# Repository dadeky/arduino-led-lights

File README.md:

# arduino-led-lights
C++ Arduino application that manages led lights dimming

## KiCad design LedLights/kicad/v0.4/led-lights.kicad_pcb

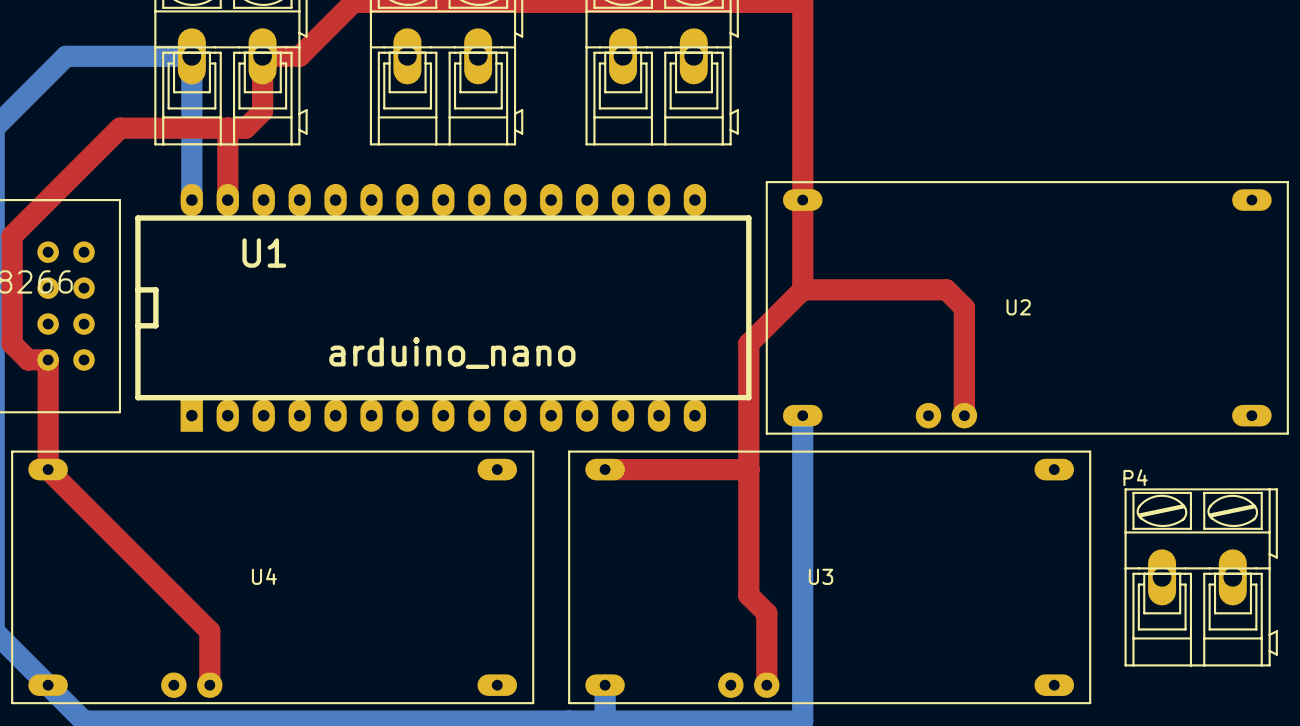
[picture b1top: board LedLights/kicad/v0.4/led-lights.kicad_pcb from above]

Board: 2 copper layers, 9 parts (0 on the bottom side), 13 nets.

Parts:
P1: Power input; AK300-2
P3: LED 1; AK300-2
P4: LED 2; AK300-2
P5: LED 3; AK300-2
U1: arduino_nano
U2, U3, U4: LED_Driver_700mA; LED_Driver_700mA_foot
U5: Wlan_ESP8266

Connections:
+12V: P1.1, U1.VIN, U2.1, U3.1, U4.1
GND: P1.2, U1.GND, U2.2, U2.6, U3.2, U3.6, U4.2, U4.6, U5.GND
unnamed: P3.1, U2.3
unnamed: P3.2, U2.4
unnamed: P4.1, U3.3
unnamed: P4.2, U3.4
unnamed: P5.1, U4.3
unnamed: P5.2, U4.4
ledPwmPin1: U1.D3, U2.5
ledPwmPin2: U1.D5, U3.5
ledPwmPin3: U1.D6, U4.5
wlanRX: U1.D7, U5.RX
wlanTX: U1.D4, U5.TX

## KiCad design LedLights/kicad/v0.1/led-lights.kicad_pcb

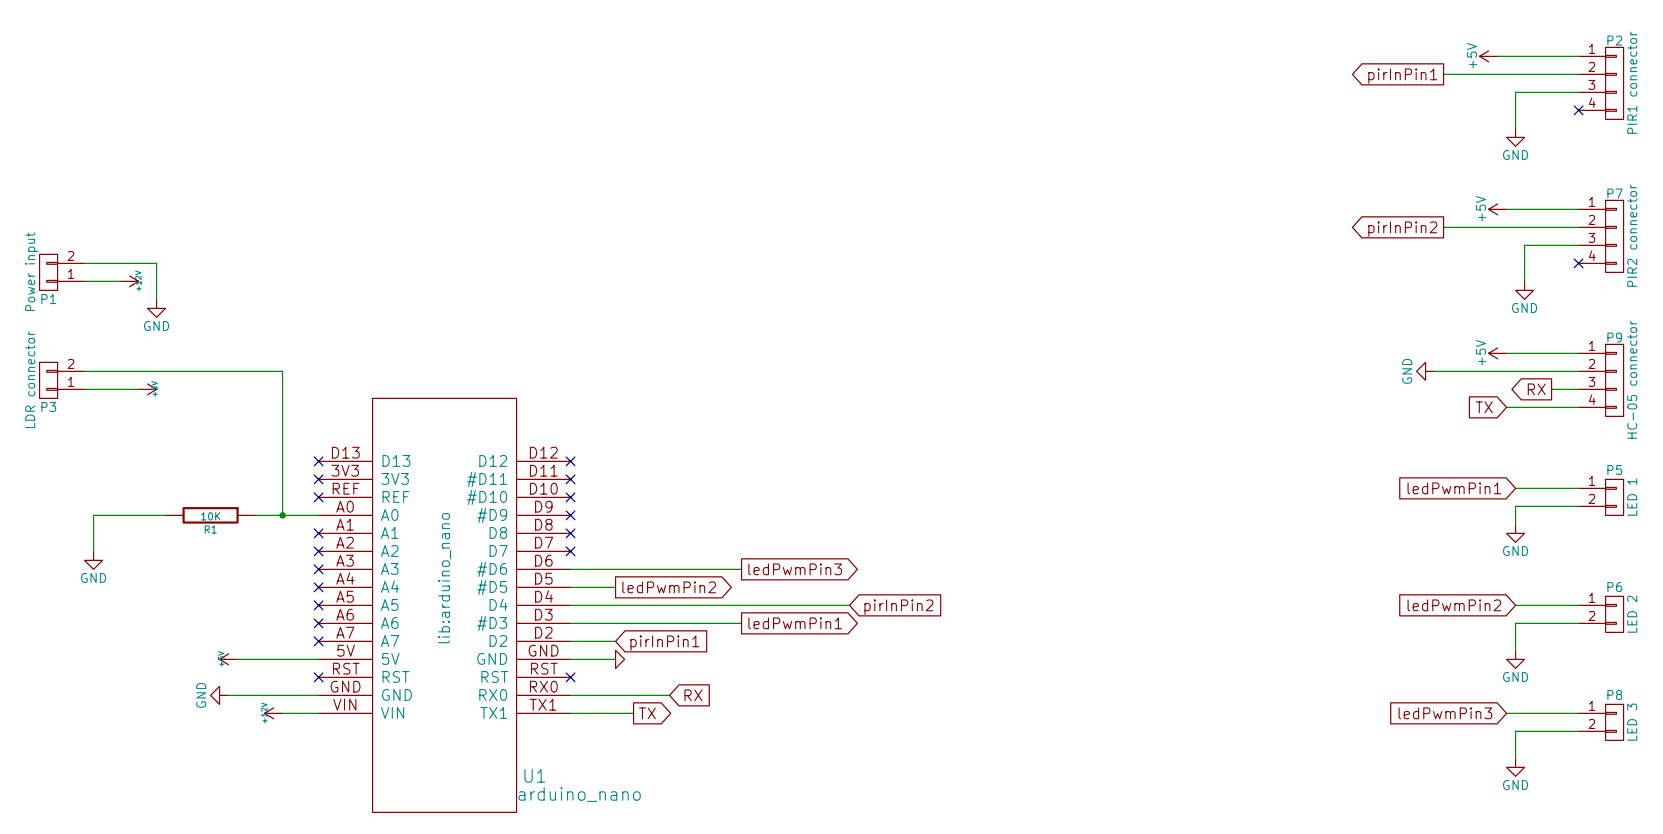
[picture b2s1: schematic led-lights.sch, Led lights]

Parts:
P1: Power input; AK300-2
P2: PIR1 connector; AK300-4
P3: LDR connector; AK300-2
P5: LED 1; AK300-2
P6: LED 2; AK300-2
P7: PIR2 connector; AK300-4
P8: LED 3; AK300-2
P9: HC-05 connector; Socket_Strip_Straight_1x04
R1: 10K; Resistor_Horizontal_RM15mm
U1: arduino_nano

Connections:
+5V: P2.1, P3.1, P7.1, P9.1, U1.5V
+12V: P1.1, U1.VIN
GND: P1.2, P2.3, P5.2, P6.2, P7.3, P8.2, P9.2, R1.2, U1.GND
unnamed: P3.2, R1.1, U1.A0
RX: P9.3, U1.RX0
TX: P9.4, U1.TX1
ledPwmPin1: P5.1, U1.D3 (#D3)
ledPwmPin2: P6.1, U1.D5 (#D5)
ledPwmPin3: P8.1, U1.D6 (#D6)
pirInPin1: P2.2, U1.D2
pirInPin2: P7.2, U1.D4

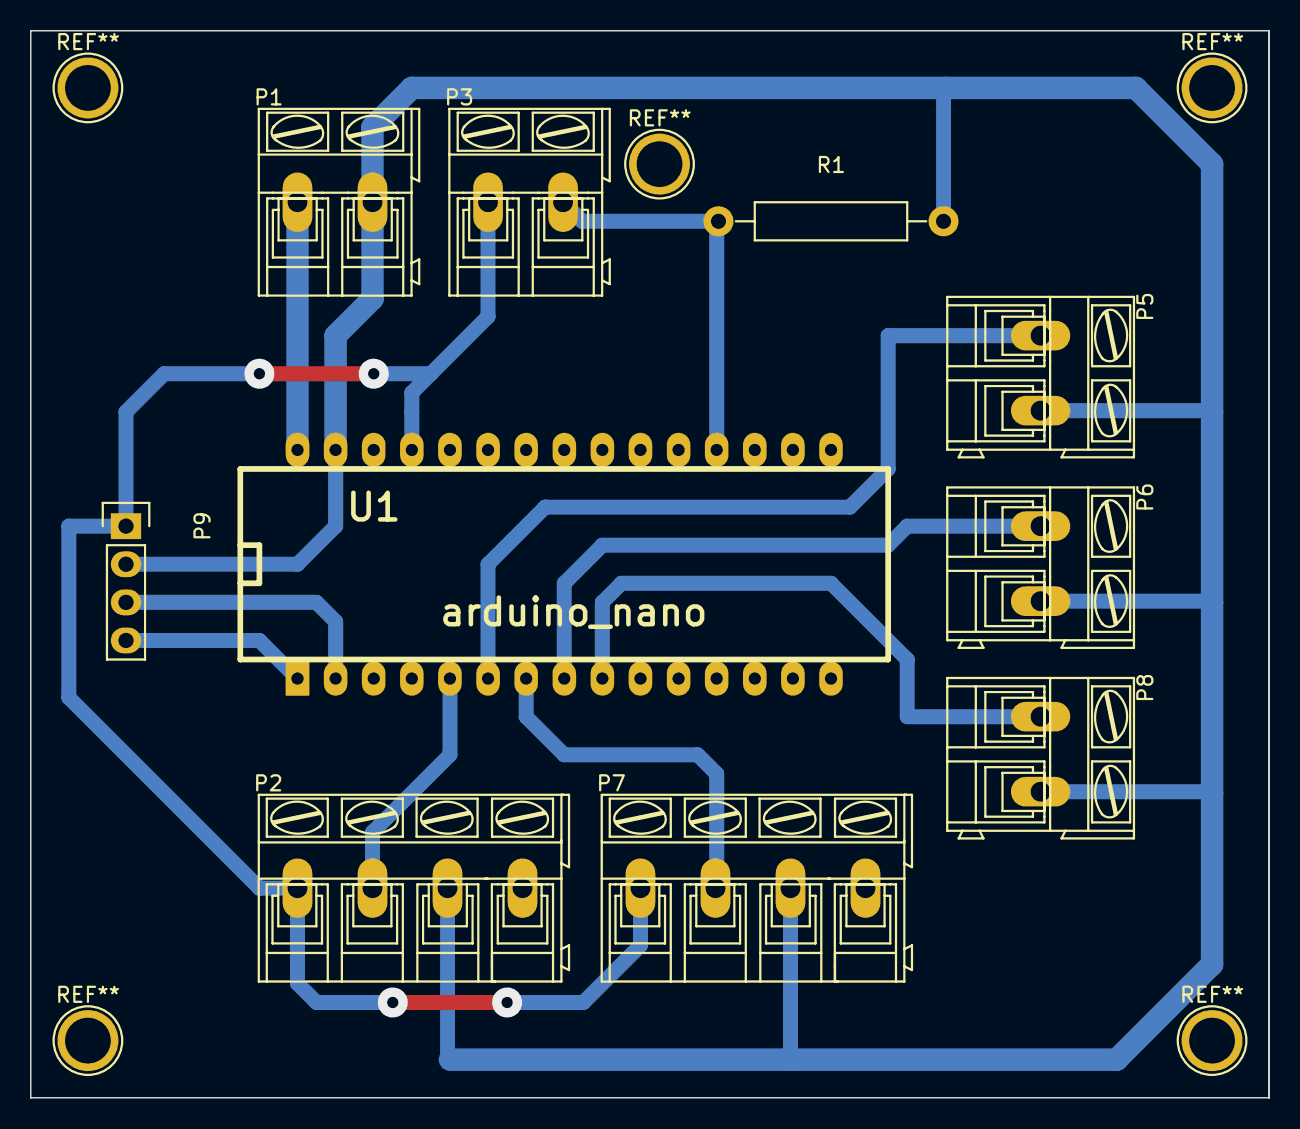
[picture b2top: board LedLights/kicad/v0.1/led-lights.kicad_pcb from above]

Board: 2 copper layers, 82.6 x 71.1 mm, 10 parts (0 on the bottom side), 11 nets.

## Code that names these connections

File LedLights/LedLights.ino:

// Do not remove the include below
#include "Arduino.h"

//pins
const int ledPwmPin1 = 3;			//the pin that is used to dim the light #1
const int ledPwmPin2 = 5;			//the pin that is used to dim the light #2
const int ledPwmPin3 = 6;			//the pin that is used to dim the light #3
const int pirInPin1 = 2;			//Passive Infrared Sensor - motion detector #1
const int pirInPin2 = 4;			//Passive Infrared Sensor - motion detector #2
const int boardLed = 13;			//onboard led
const int photoResistorPin = A0;	//pin that reads the photoresistor1

//runtime vars
int pirVal1;							//the value of PIR1 sensor
int pirVal2;							//the value of PIR2 sensor
bool lightTurnedOn = false;				//is the light currently turned on
int turnOnDelay = 7;					//number of miliseconds to step up the pwm by one
int turnOnShift = 100;
int turnOffDelay = 10;					//number of miliseconds to step down the pwm by one
int photoResistorThreshold = 500;		//at which light intensity the PIR functionality is turned on
int photoVal;							//stores the value of photo-resistor

void setup()
{
	pinMode(ledPwmPin1,OUTPUT);
	pinMode(ledPwmPin2,OUTPUT);
	pinMode(ledPwmPin3,OUTPUT);
	pinMode(pirInPin1,INPUT);
	pinMode(pirInPin2,INPUT);
	pinMode(boardLed,OUTPUT);
	analogWrite(ledPwmPin1,255);
	analogWrite(ledPwmPin2,255);
	analogWrite(ledPwmPin3,255);
	//Serial.begin(9600);
}

void loop()
{
	/*Serial.println(analogRead(photoResistorPin));
	delay(1000);*/
	pirVal1 = digitalRead(pirInPin1);
	pirVal2 = digitalRead(pirInPin2);
	photoVal = analogRead(photoResistorPin);
		if(pirVal1 == HIGH/* || pirVal2 == HIGH*/){
			if(photoVal < photoResistorThreshold){
				turnOnTheLight();
			}
		}else{
			turnOffTheLight();
		}
}

void turnOnTheLight()
{
	if(!lightTurnedOn){
		digitalWrite(boardLed,HIGH);
		int totalCycles = turnOnShift * 2 + 255;
		for(int i=0; i <= totalCycles; i++){
			if(i>=0 && i<=255){
				int j = map(i,0,255,255,0);
				analogWrite(ledPwmPin1,j);
			}

			if(i>=turnOnShift && i<=turnOnShift+255){
				int k = map(i,turnOnShift,turnOnShift+255,255,0);
				analogWrite(ledPwmPin2,k);
			}

			if(i>=turnOnShift*2 && i<=turnOnShift*2+255){
				int l = map(i,turnOnShift*2,turnOnShift*2+255,255,0);
				analogWrite(ledPwmPin3,l);
			}

			delay(turnOnDelay);
		}
		lightTurnedOn = true;
	}
}

void turnOffTheLight()
{
	if(lightTurnedOn){
		for(int i=0; i <= 255; i++){
			if(i>=0 && i<=255){
				analogWrite(ledPwmPin1,i);
				analogWrite(ledPwmPin2,i);
				analogWrite(ledPwmPin3,i);
			}
			delay(turnOffDelay);
		}
	}
	lightTurnedOn = false;
	digitalWrite(boardLed,LOW);
}

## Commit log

2015-07-27 Post initial commit
2015-07-27 Project files
2015-08-18 lang
2015-09-10 Photoresistor added.
2015-09-15 Final version.
2015-09-21 KiCad stuff, schema, and pcb
2015-09-24 KiCad + program change.
2015-09-24 kicad
2015-09-30 PCB finished, housing started.
2015-10-09 Kicad changes.
2016-01-10 freecad
2016-01-11 3D printer file
2016-06-08 Compiled with V3
2017-12-28 new sloeber version
2018-01-03 version 0.2 of the board added
2018-01-08 Kicad and stuff
2018-01-08 One too many include.
2018-06-18 WiFi introduced
2018-06-18 Compiled
2018-06-22 Some
2018-06-29 enum added
2018-07-12 Photon
2018-09-09 New versions of pcb added
